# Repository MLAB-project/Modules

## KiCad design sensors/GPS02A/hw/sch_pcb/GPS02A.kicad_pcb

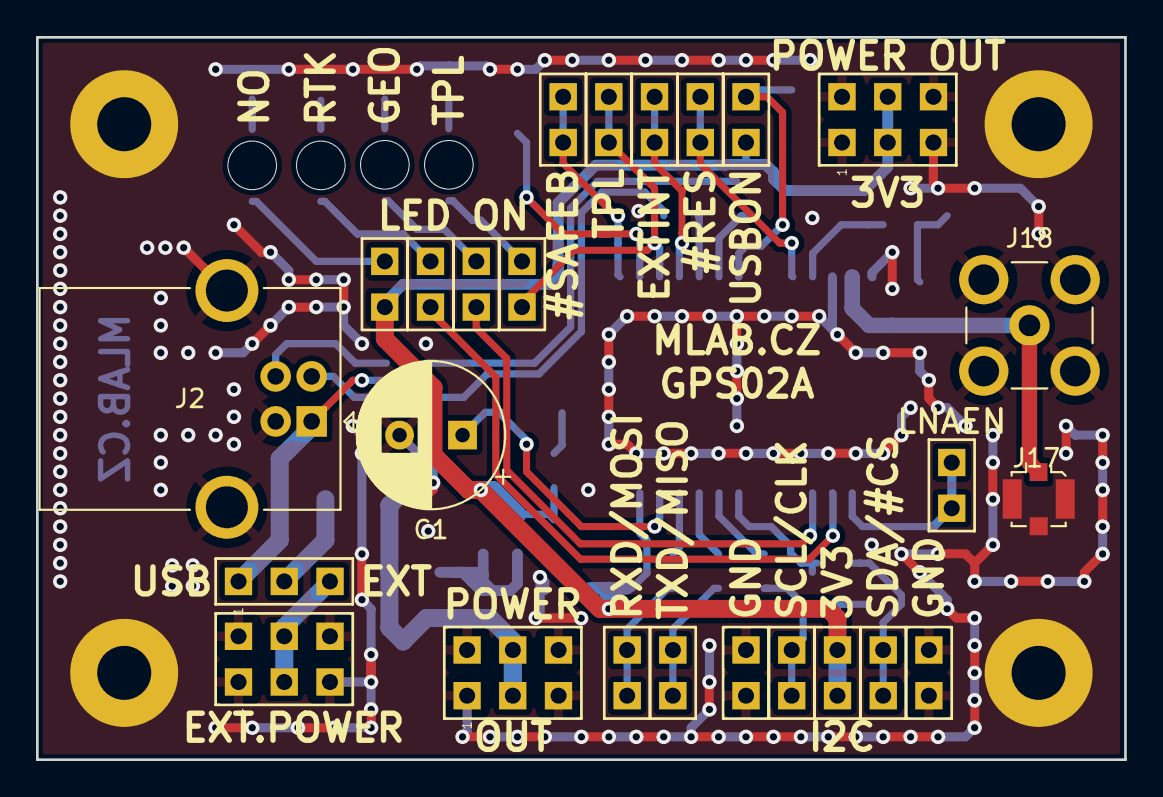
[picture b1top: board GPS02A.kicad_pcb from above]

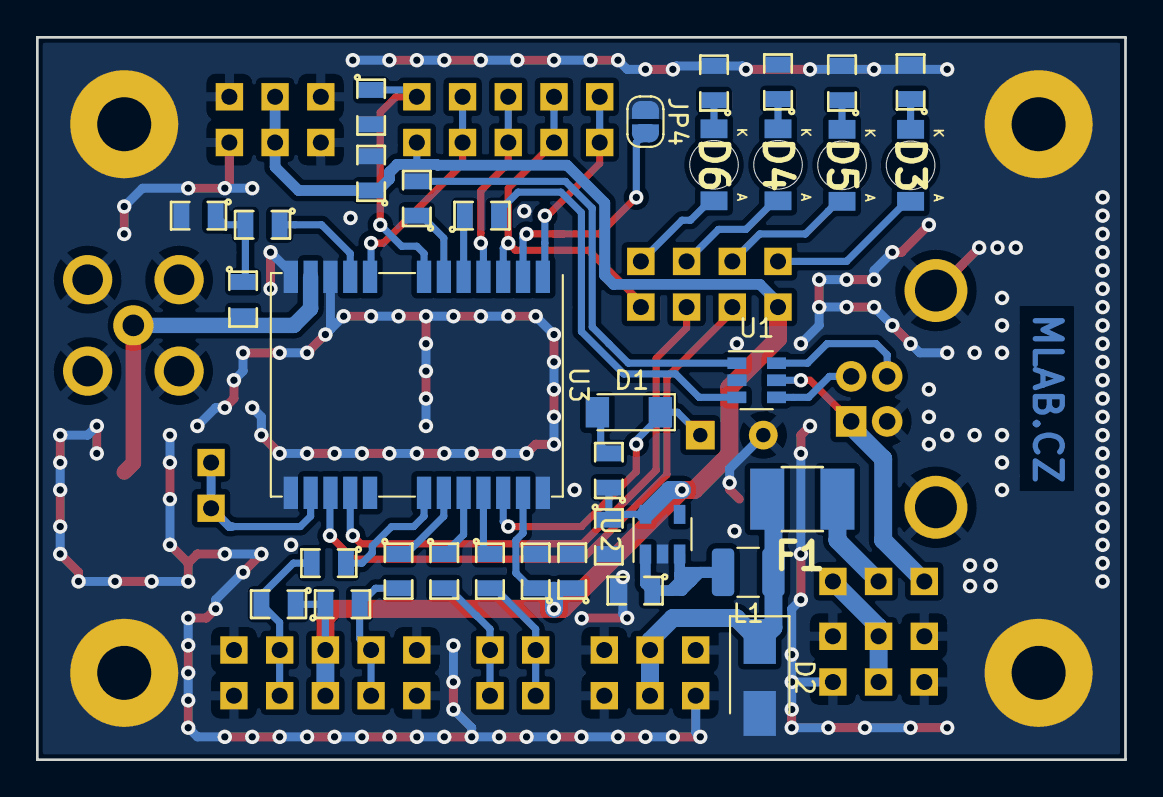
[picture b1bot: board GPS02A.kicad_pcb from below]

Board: 2 copper layers, 60.5 x 40.1 mm, 63 parts (34 on the bottom side), 43 nets.

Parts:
C1: 1F; CP_Radial_D8.0mm_P3.50mm
C2: 10uF; SMD-0805
C3, C5, C6: 1uF; SMD-0805
C4: 100nF; SMD-0805
C7: 10nF; SMD-0805
D1: BAS85; D_MiniMELF
D2: M4; D_SMA
D3: RED; LED_1206
D4, D5: YELLOW; LED_1206
D6: GREEN; LED_1206
F1: 750mA; 1812
J1, J3, J15: HEADER_2x03_PARALLEL; Straight_2x03
J2: USB_B; USB_B_OST_USB-B1HSxx_Horizontal
J4, J5, J6, J7, J8, J9, J10, J11, J12, J13, J14, J16: HEADER_2x01_PARALLEL; Straight_2x01
J17: u.FL; U.FL_Molex_MCRF_73412-0110_Vertical
J18: SMA; SMB_Jack_Vertical
JP1: Jumper_3_Bridged12; Straight_1x03
JP2, JP6: Jumper_2_Bridged; Straight_1x02
JP4: Jumper_2_Open; SolderJumper-2_P1.3mm_Open_RoundedPad1.0x1.5mm
JP7, JP8, JP9: Jumper_2_Open; Straight_1x02
L1: NL322522T-101K; L_1210_3225Metric
L2: 27nH; SMD-0805
M1, M2, M3, M4: HOLE; MountingHole_3mm
R1: 22R; SMD-0805
R2, R3, R15: 10k; SMD-0805
R4, R5, R6, R7, R8, R9: 33R; SMD-0805
R10, R12, R13, R14: 620R; SMD-0805
R11: 10R; SMD-0805
U1: USBLC6-2SC6; SOT-23-6
U2: MIC5504-3.3YM5; SOT-23-5
U3: NEO-M8P; ublox_NEO

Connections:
+3V3: C3.1, C4.1, C5.1, C6.1, J8.1, J8.2, J15.3, J15.4, JP2.2, JP9.1, R1.1, R2.1, R3.1, U2.5, U3.23
/#RESET: J13.1, J13.2, U3.8
/#SAFEB: J12.1, J12.2, U3.1
/D+: J2.3, U1.6
/D-: J2.2, U1.4
/DM: R4.2, U1.3
/DP: R5.2, U1.1
/D_SEL: JP4.2, U3.2
/EXTINT: J11.1, J11.2, U3.4
/GEO_STAT: D4.2, JP8.2
/LNEN: J14.1, J14.2, U3.14
/RTK_STAT: D5.2, JP7.2
/RXD/MOSI: J5.1, J5.2, R7.2
/SCL/CLK: J7.1, J7.2, R3.2, R9.2
/SDA/#CS: J6.1, J6.2, R2.2, R8.2
/TIMEPULSE: D6.2, JP6.2
/TXD/MISO: J4.1, J4.2, R6.2
/VBACKUP: C1.1, D1.1, U3.22
/VBUS: J2.1, JP1.1, U1.5
/VDD_USB: JP2.1, R15.1, U3.7
GND: C1.2, C2.2, C3.2, C4.2, C5.2, C6.2, C7.2, D2.2, J1.1, J1.2, J1.5, J1.6, J2.4, J2.5, J3.1, J3.2, J3.5, J3.6, J9.1, J9.2, J10.1, J10.2, J15.1, J15.2, J15.5, J15.6, J17.2, J18.2, JP4.1, M1.1, M2.1, M3.1, M4.1, R10.2, R12.2, R13.2, R14.2, R15.2, U1.2, U2.2, U3.10, U3.12, U3.13, U3.24
unnamed: C2.1, L1.2, U2.1, U2.3
unnamed: C7.1, L2.1, R11.2
unnamed: D1.2, R1.2
unnamed: D2.1, F1.2, J3.3, J3.4, L1.1
unnamed: D3.1, R10.1
unnamed: D3.2, JP9.2
unnamed: D4.1, R12.1
unnamed: D5.1, R13.1
unnamed: D6.1, R14.1
unnamed: F1.1, JP1.2
unnamed: J1.3, J1.4, JP1.3
unnamed: J16.1, J16.2, JP6.1, U3.3
unnamed: J17.1, J18.1, L2.2, U3.11
unnamed: JP7.1, U3.15
unnamed: JP8.1, U3.16
unnamed: R4.1, U3.5
unnamed: R5.1, U3.6
unnamed: R6.1, U3.20
unnamed: R7.1, U3.21
unnamed: R8.1, U3.18
unnamed: R9.1, U3.19
unnamed: R11.1, U3.9

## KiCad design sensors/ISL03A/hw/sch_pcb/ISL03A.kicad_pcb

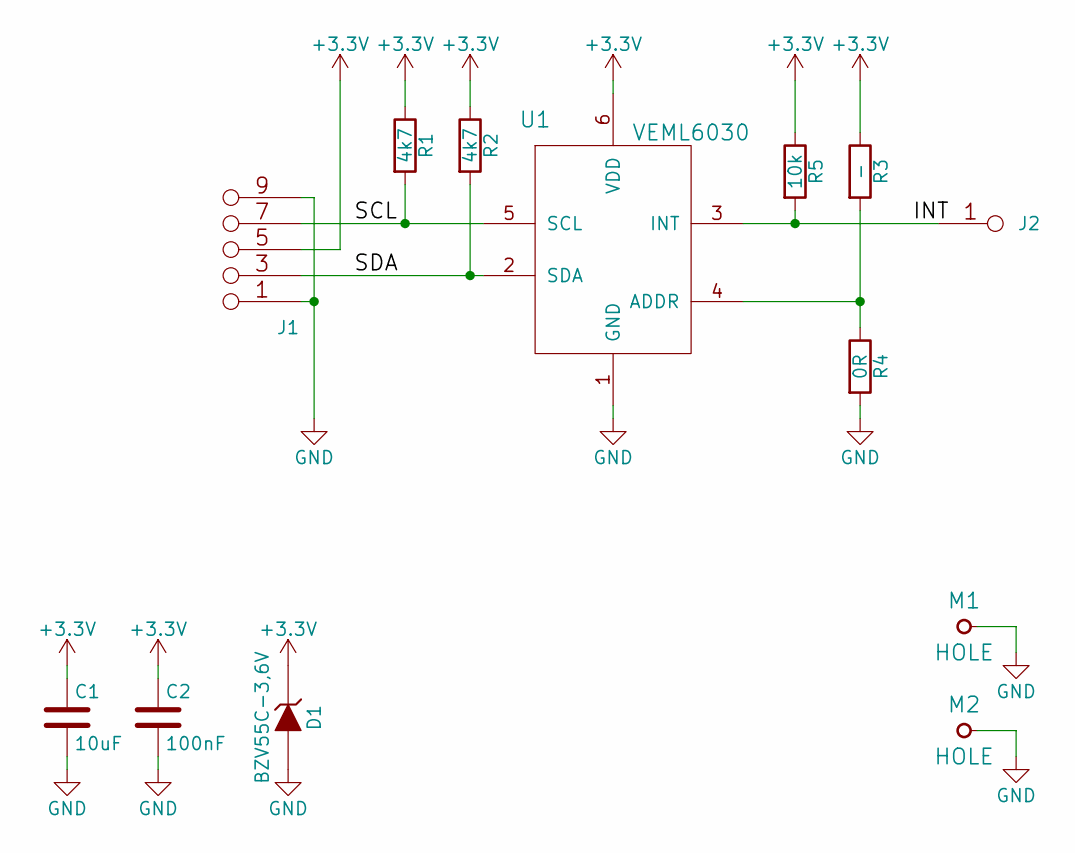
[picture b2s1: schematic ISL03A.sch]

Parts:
C1: 10uF; SMD-0805
C2: 100nF; SMD-0805
D1: BZV55C-3,6V; Diode-MiniMELF_Standard
J1: JUMP_5X2; Straight_2x05
J2: CONN1_1; Straight_1x01
M1, M2: HOLE; MountingHole_3mm
R1, R2: 4k7; SMD-0805
R3: -; SMD-0805
R4: 0R; SMD-0805
R5: 10k; SMD-0805
U1: VEML6030

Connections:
+3V3: C1.1, C2.1, D1.2 (K), J1.5 (6), J1.6, R1.1, R2.1, R3.1, R5.1, U1.6 (VDD)
/INT: J2.1, R5.2, U1.3 (INT)
/SCL: J1.7, J1.8 (7), R1.2, U1.5 (SCL)
/SDA: J1.3 (4), J1.4, R2.2, U1.2 (SDA)
GND: C1.2, C2.2, D1.1 (A), J1.1 (2), J1.2, J1.9 (10), J1.10, M1.1, M2.1, R4.2, U1.1 (GND)
unnamed: R3.2, R4.1, U1.4 (ADDR)

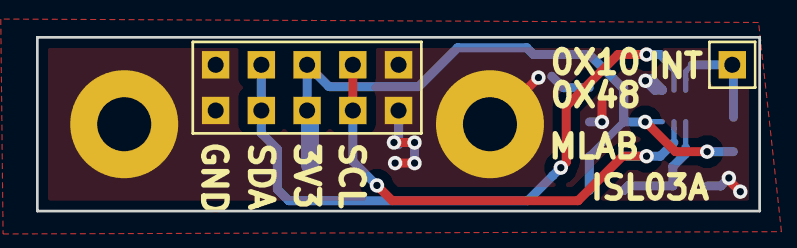
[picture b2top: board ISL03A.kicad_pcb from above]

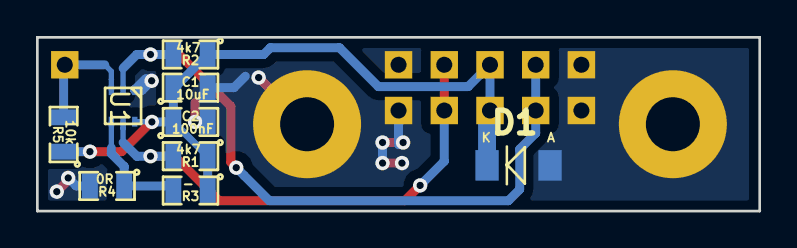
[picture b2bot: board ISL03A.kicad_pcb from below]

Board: 2 copper layers, 40.1 x 9.7 mm, 13 parts (9 on the bottom side), 6 nets.

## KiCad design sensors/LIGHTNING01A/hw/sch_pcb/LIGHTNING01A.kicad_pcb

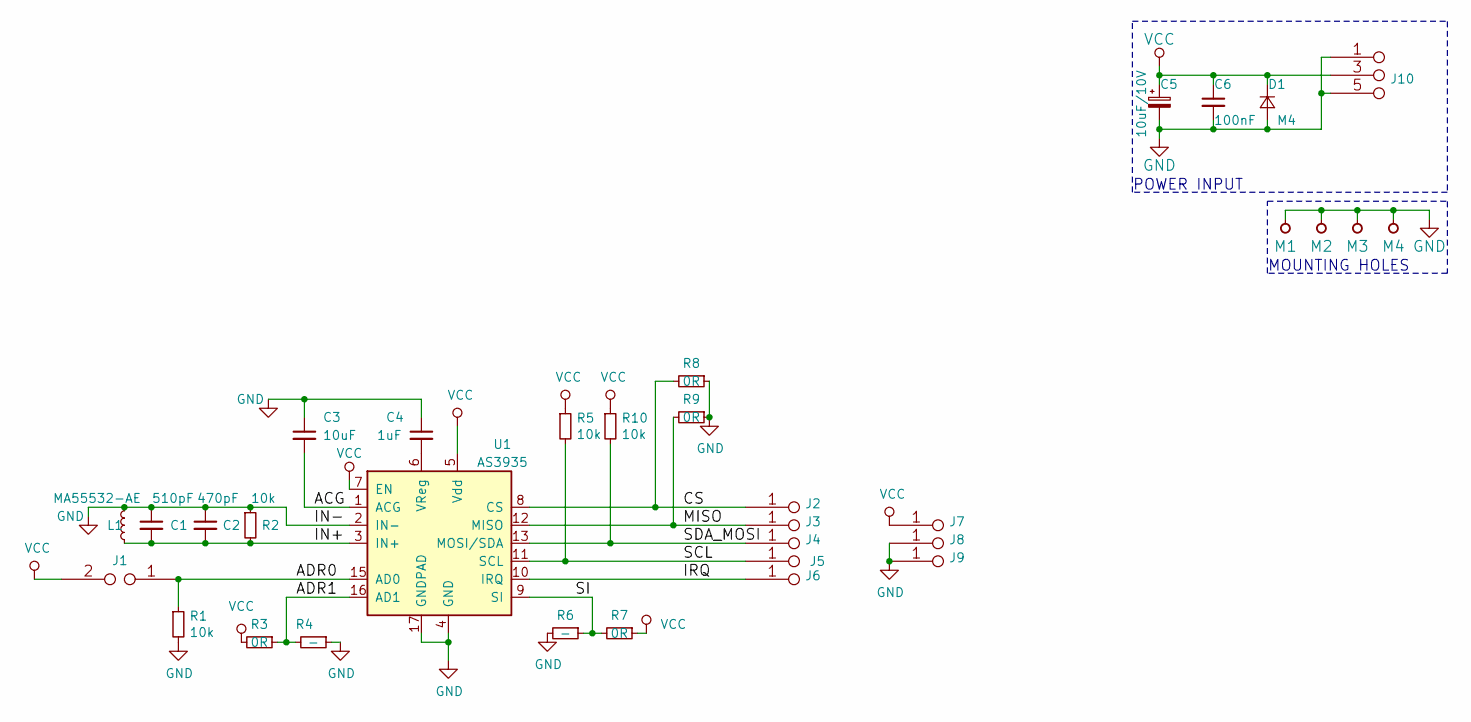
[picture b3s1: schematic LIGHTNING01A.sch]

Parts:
C1: 510pF; SMD-0805
C2: 470pF; SMD-0805
C3: 10uF; SMD-0805
C4: 1uF; SMD-0805
C5: 10uF/10V; SMD-0805
C6: 100nF; SMD-0805
D1: M4; Diode-MELF_Standard
J1: JUMP2_2x1; Straight_2x01
J2, J3, J4, J5, J6, J7, J8, J9: JUMP_2x1; Straight_2x01
J10: JUMP_3X2; Straight_2x03
L1: MA55532-AE; Coilcraft_MA5532-AE_RFID
M1, M2, M3, M4: HOLE; MountingHole_3mm
R1, R2, R5, R10: 10k; SMD-0805
R3, R7, R8, R9: 0R; SMD-0805
R4, R6: -; SMD-0805
U1: AS3935; MLPQ-16

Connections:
/ACG: C3.2, U1.1 (ACG)
/ADR0: J1.1, R1.1, U1.15 (AD0)
/ADR1: R3.1, R4.2, U1.16 (AD1)
/CS: J2.1, J2.2, R8.2, U1.8 (CS)
/IN+: C1.2, C2.2, L1.1, R2.2, U1.3 (IN+)
/IRQ: J6.1, J6.2, U1.10 (IRQ)
/MISO: J3.1, J3.2, R9.2, U1.12 (MISO)
/SCL: J5.1, J5.2, R5.2, U1.11 (SCL)
/SDA_MOSI: J4.1, J4.2, R10.2, U1.13 (MOSI/SDA)
/SI: R6.1, R7.2, U1.9 (SI)
GND: C1.1, C2.1, C3.1, C4.1, C5.2, C6.2, D1.2 (A), J8.1, J8.2, J9.1, J9.2, J10.1 (2), J10.2, J10.5 (6), J10.6, L1.2, M1.1, M2.1, M3.1, M4.1, R1.2, R2.1, R4.1, R6.2, R8.1, R9.1, U1.2 (IN-), U1.4 (GND), U1.17 (GNDPAD)
unnamed: C4.2, U1.6 (VReg)
VCC: C5.1, C6.1, D1.1 (K), J1.2, J7.1, J7.2, J10.3 (4), J10.4, R3.2, R5.1, R7.1, R10.1, U1.5 (Vdd), U1.7 (EN)

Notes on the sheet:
POWER INPUT
MOUNTING HOLES

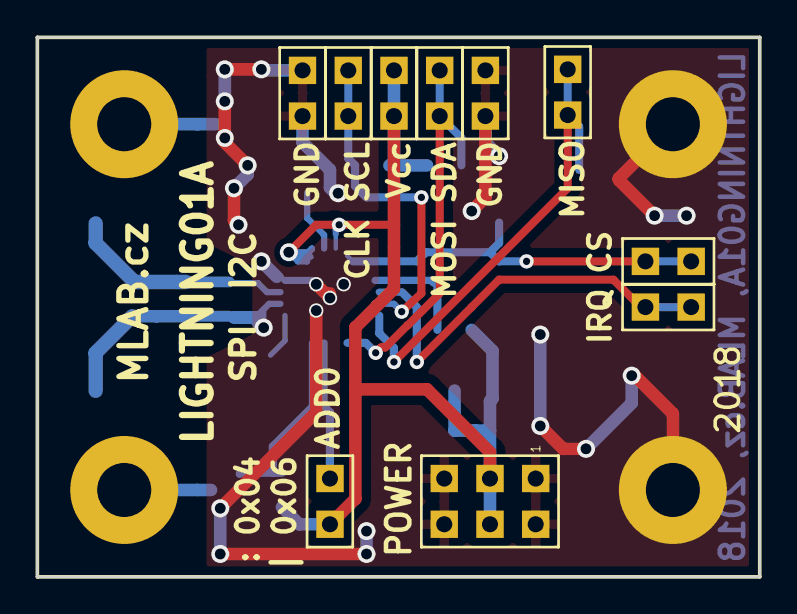
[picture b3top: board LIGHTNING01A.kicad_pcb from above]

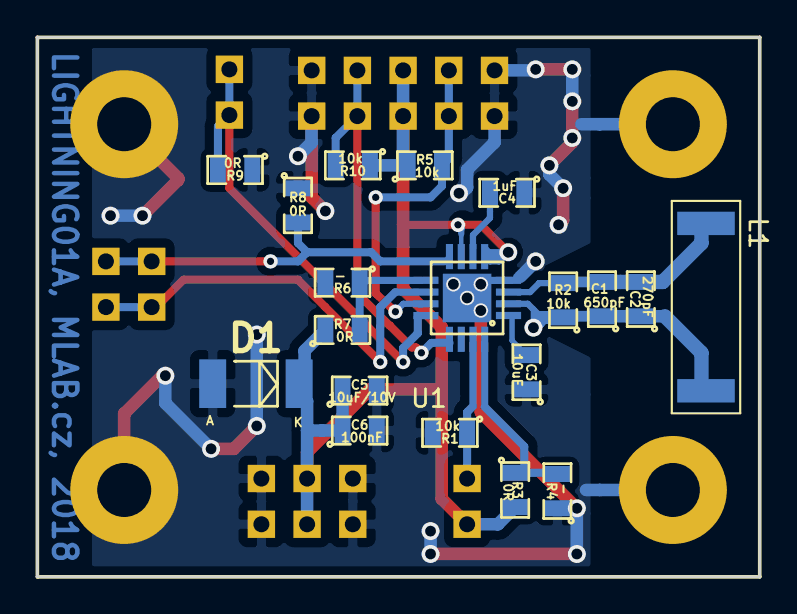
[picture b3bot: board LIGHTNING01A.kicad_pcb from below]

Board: 2 copper layers, 40.1 x 30.0 mm, 33 parts (19 on the bottom side), 13 nets.

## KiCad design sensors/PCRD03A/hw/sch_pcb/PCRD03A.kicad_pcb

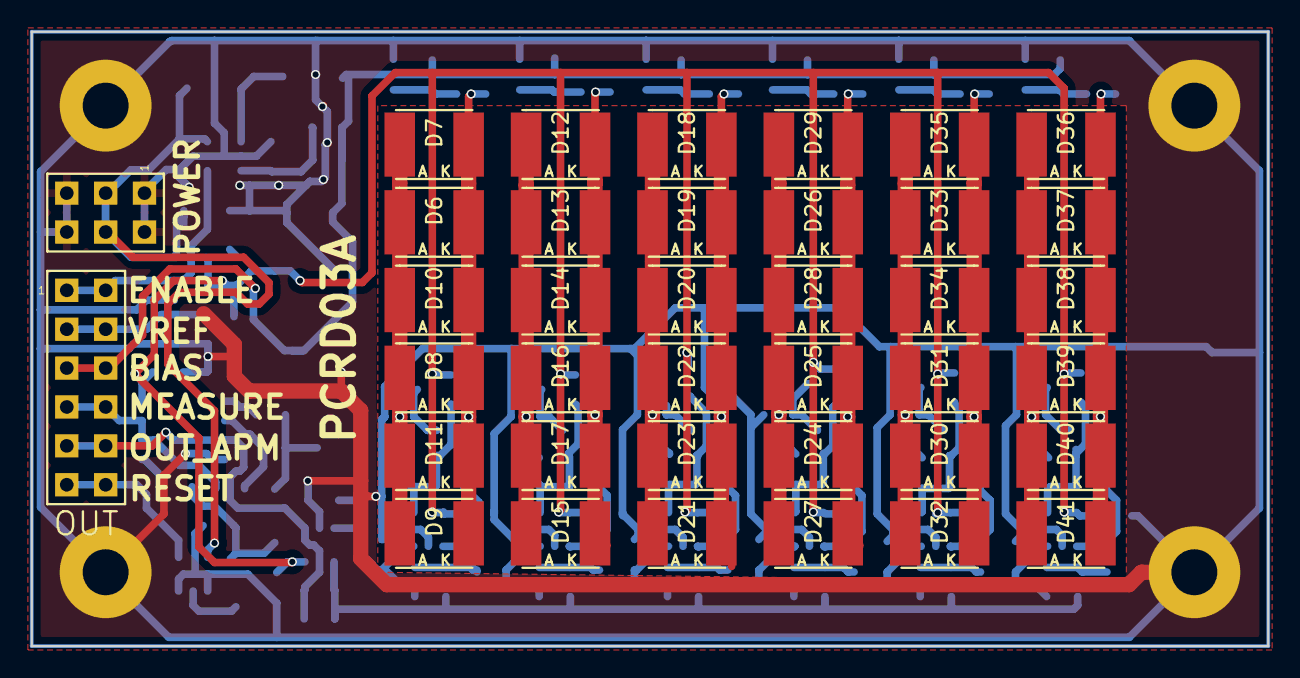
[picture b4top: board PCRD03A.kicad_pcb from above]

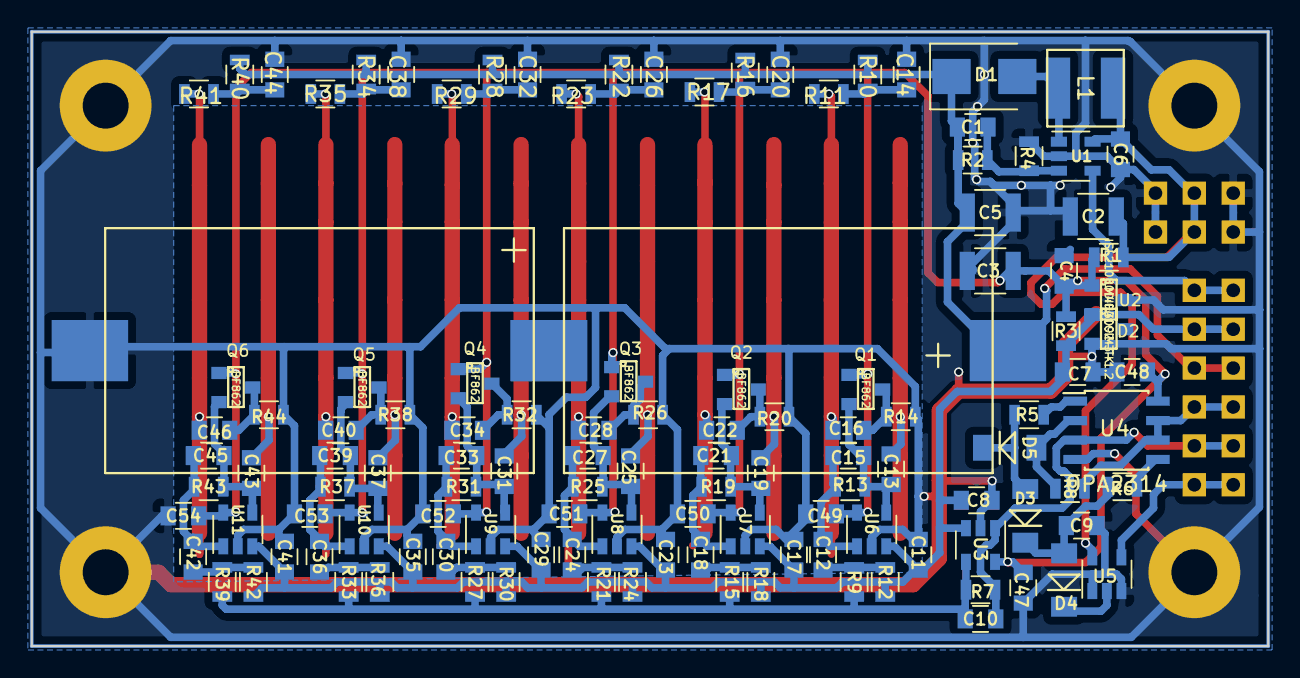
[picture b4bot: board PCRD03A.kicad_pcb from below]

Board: 2 copper layers, 80.8 x 40.1 mm, 165 parts (123 on the bottom side), 61 nets.

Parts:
BT1, BT2: Battery_Cell; CH28-2032
C1: 22p; C_0805
C2, C3, C5: 47u/16V; C_1210
C4, C7, C47, C48, C49, C50, C51, C52, C53, C54: 100n; C_0805
C6, C8, C11, C16, C17, C22, C23, C28, C29, C34, C35, C40, C41, C46: 4u7; C_0805
C9, C13, C19, C25, C31, C37, C43: 1n; C_0805
C10: 2n2; C_0805
C12, C14, C18, C20, C24, C26, C30, C32, C36, C38, C42, C44: 1u; C_0805
C15, C21, C27, C33, C39, C45: 1p; C_0805
D1: STPS1L30U; D_SMB
D2: LM4041CIM3-1.2; SOT-23
D3, D4, D5: 1N4148; Diode-MiniMELF_Standard
D6, D7, D8, D9, D10, D11, D12, D13, D14, D15, D16, D17, D18, D19, D20, D21, D22, D23, D24, D25, D26, D27, D28, D29, D30, D31, D32, D33, D34, D35, D36, D37, D38, D39, D40, D41: D_Photo; PIND_universal
J1: POWER; Straight_2x03
J2: OUT; Straight_2x06
L1: 10u; DJNR5040
M1, M2, M3, M4: HOLE; MountingHole_3mm
Q1, Q2, Q3, Q4, Q5, Q6: BF862; SOT-23
R1: 100/10; R_0805
R2: 470k; R_0805
R3, R10, R11, R16, R17, R22, R23, R28, R29, R34, R35, R40, R41: 4k7; R_0805
R4: 120k; R_0805
R5, R6, R8, R9, R15, R21, R27, R33, R39: 1k; R_0805
R7: 22k; R_0805
R12, R14, R18, R20, R24, R26, R30, R32, R36, R38, R42, R44: 3k3; R_0805
R13, R19, R25, R31, R37, R43: 10M; R_0805
U1: TPS6104; SOT-23-5
U2: ISL21080DIH309Z-TK; SOT-23
U3, U6, U7, U8, U9, U10, U11: OPA314; SOT-23-5
U4: OPA2314; SOIC-8_3.9x4.9mm_Pitch1.27mm
U5: TS5A4594; SOT-23-5

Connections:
+3V3: C3.1, C4.1, C47.1, C48.1, C49.1, C50.1, C51.1, C52.1, C53.1, C54.1, Q1.1, Q2.1, Q3.1, Q4.1, Q5.1, Q6.1, R1.1, R3.2, U2.1, U3.5, U4.8, U6.5, U7.5, U8.5, U9.5, U10.5, U11.5
+BATT: C2.1, C6.1, J1.3, J1.4, L1.1, R1.2, U1.5, U5.5
/BIAS: BT1.1, C1.1, C5.1, D1.1, J2.5, J2.6, R2.1, R10.2, R16.2, R22.2, R28.2, R34.2, R40.2
/ENABLE: J2.1, J2.2, U1.4
/MEASURE: J2.7, J2.8, R8.1, U4.6, U4.7
/OUT_AMP: C10.1, J2.9, J2.10, R7.1, U3.1, U4.3
/RESET: J2.11, J2.12, U5.4
/VREF: C7.1, C8.2, C11.2, C17.2, C23.2, C29.2, C35.2, C41.2, D2.1, J2.3, J2.4, R3.1, R12.1, R18.1, R24.1, R30.1, R36.1, R42.1, U2.2, U3.3, U6.3, U7.3, U8.3, U9.3, U10.3, U11.3
/charge_amp1/OUT: C10.2, R7.2, R9.1, R15.1, R21.1, R27.1, R33.1, R39.1, U3.4
GND: BT2.2, C2.2, C3.2, C4.2, C5.2, C6.2, C7.2, C8.1, C9.2, C11.1, C14.1, C17.1, C20.1, C23.1, C26.1, C29.1, C32.1, C35.1, C38.1, C41.1, C44.1, C47.2, C48.2, C49.2, C50.2, C51.2, C52.2, C53.2, C54.2, D2.2, J1.1, J1.2, J1.5, J1.6, M1.1, M2.1, M3.1, M4.1, R4.2, R14.1, R20.1, R26.1, R32.1, R38.1, R44.1, U1.2, U2.3, U3.2, U4.4, U5.1, U5.3, U6.2, U7.2, U8.2, U9.2, U10.2, U11.2
unnamed: BT1.2, BT2.1
unnamed: C1.2, R2.2, R4.1, U1.3
unnamed: C9.1, D3.1, D4.2, R6.2
unnamed: C12.1, C15.1, R13.1, U6.1
unnamed: C12.2, R9.2, R12.2
unnamed: C13.1, D6.2, D7.2, D8.2, D9.2, D10.2, D11.2
unnamed: C13.2, C15.2, Q1.2, R13.2, U6.4
unnamed: C14.2, R10.1, R11.2
unnamed: C16.1, D6.1, D7.1, D8.1, D9.1, D10.1, D11.1, R11.1
unnamed: C16.2, Q1.3, R14.2
unnamed: C18.1, C21.1, R19.1, U7.1
unnamed: C18.2, R15.2, R18.2
unnamed: C19.1, D12.2, D13.2, D14.2, D15.2, D16.2, D17.2
unnamed: C19.2, C21.2, Q2.2, R19.2, U7.4
unnamed: C20.2, R16.1, R17.2
unnamed: C22.1, D12.1, D13.1, D14.1, D15.1, D16.1, D17.1, R17.1
unnamed: C22.2, Q2.3, R20.2
unnamed: C24.1, C27.1, R25.1, U8.1
unnamed: C24.2, R21.2, R24.2
unnamed: C25.1, D18.2, D19.2, D20.2, D21.2, D22.2, D23.2
unnamed: C25.2, C27.2, Q3.2, R25.2, U8.4
unnamed: C26.2, R22.1, R23.2
unnamed: C28.1, D18.1, D19.1, D20.1, D21.1, D22.1, D23.1, R23.1
unnamed: C28.2, Q3.3, R26.2
unnamed: C30.1, C33.1, R31.1, U9.1
unnamed: C30.2, R27.2, R30.2
unnamed: C31.1, D24.2, D25.2, D26.2, D27.2, D28.2, D29.2
unnamed: C31.2, C33.2, Q4.2, R31.2, U9.4
unnamed: C32.2, R28.1, R29.2
unnamed: C34.1, D24.1, D25.1, D26.1, D27.1, D28.1, D29.1, R29.1
unnamed: C34.2, Q4.3, R32.2
unnamed: C36.1, C39.1, R37.1, U10.1
unnamed: C36.2, R33.2, R36.2
unnamed: C37.1, D30.2, D31.2, D32.2, D33.2, D34.2, D35.2
unnamed: C37.2, C39.2, Q5.2, R37.2, U10.4
unnamed: C38.2, R34.1, R35.2
unnamed: C40.1, D30.1, D31.1, D32.1, D33.1, D34.1, D35.1, R35.1
unnamed: C40.2, Q5.3, R38.2
unnamed: C42.1, C45.1, R43.1, U11.1
unnamed: C42.2, R39.2, R42.2
unnamed: C43.1, D36.2, D37.2, D38.2, D39.2, D40.2, D41.2
unnamed: C43.2, C45.2, Q6.2, R43.2, U11.4
unnamed: C44.2, R40.1, R41.2
unnamed: C46.1, D36.1, D37.1, D38.1, D39.1, D40.1, D41.1, R41.1
unnamed: C46.2, Q6.3, R44.2
unnamed: D1.2, L1.2, U1.1
unnamed: D3.2, D5.1, R5.1
unnamed: D4.1, U5.2
unnamed: D5.2, R8.2, U4.2
unnamed: R5.2, U4.1
unnamed: R6.1, U4.5

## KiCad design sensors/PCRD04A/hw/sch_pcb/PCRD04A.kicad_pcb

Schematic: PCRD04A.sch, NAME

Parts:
BT1: CH28-2032
C1: 47uF; TantalC_SizeC_Reflow
C2: 1uF/36V; SMD-0805
C3, C17: 4u7; SMD-0805
C4, C6, C7, C8, C9: 10uF; SMD-0805
C5: 1pF - 251R15S1R0AV4E; SMD-0805
C10, C11, C12, C13, C14, C16, C20: 100nF; SMD-0805
C15: 3n3; SMD-0805
C18: 2n2; SMD-0805
C19: 1nF; SMD-0805
D1: M4; Diode-SMA_Standard
D2: D_Photo; HAMAMATSU_S2744-09
J1: 3.6V; Straight_2x03
J2, J3, J4, J5, J6, J7: HEADER_2x01_PARALLEL; Straight_2x01
J8: HEADER_2x03_PARALLEL; Straight_2x03
J9: HEADER_1x02; Straight_1x02
J10: HEADER_1x02; Straight_2x02
M1, M2, M3, M4, M5, M6: HOLE; MountingHole_3mm
R1, R11, R14: 4k7; SMD-0805
R2, R3, R4, R5: 100; SMD-0805
R6: 10M; SMD-0805
R7, R12: 10k; SMD-0805
R8, R10: 1k; SMD-0805
R9: 15k; SMD-0805
R13: 2k2; SMD-0805
R15: -; SMD-0805
U1, U2: OPA2314; SOIC-8_3.9x4.9mm_Pitch1.27mm
U3: ISL21080DIH312Z-TK 1V25; SOT-23
U4: TS7211; SOT-23-5_HandSoldering
U5: TS5A4594; SOT-23-5_HandSoldering
U6: LM4041CIM3-1.2(neosazovat); SOT-23

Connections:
/#PeakDetect/Trace: J3.1, J3.2, R12.1, U5.4
/A: C5.2, D2.2, J10.2, R6.2, U1.2
/A/D: J6.1, J6.2, U2.6, U2.7, U4.4
/BAT+: BT1.1, D2.1, J9.2, J10.1, R14.2
/BAT-: BT1.2, C3.1, C17.1, C20.1, J9.1, R7.1, R8.2, R15.1, U1.3, U2.3, U3.2 (Vout), U6.1
/Ubias: J8.3, J8.4, R1.1
/VCC1: C6.1, C11.1, R2.1, U1.8
/VCC2: C7.1, C12.1, R3.1, U2.8
/VCC3: C8.1, C13.1, R4.1, U4.2
/VCC4: C9.1, C14.1, R5.1, U5.5
GND: C1.2, C2.2, C3.2, C4.2, C6.2, C7.2, C8.2, C9.2, C11.2, C12.2, C13.2, C14.2, C17.2, C19.2, C20.2, D1.2, J1.1, J1.2, J1.5, J1.6, J2.1, J2.2, J4.1, J4.2, J5.1, J5.2, J7.1, J7.2, J8.1, J8.2, J8.5, J8.6, M1.1, M2.1, M3.1, M4.1, M5.1, M6.1, U1.4, U2.4, U3.3 (GND), U4.5, U5.3, U6.2
unnamed: C2.1, R1.2, R14.1
unnamed: C10.1, R7.2, U1.5
unnamed: C5.1, C10.2, R6.1, U1.1
unnamed: C15.1, C16.2, R9.1, U1.7
unnamed: C15.2, R8.1, R9.2, U1.6
unnamed: C16.1, R10.2
unnamed: C18.1, R11.1, U2.1, U4.3, U5.1
unnamed: C18.2, R10.1, R11.2, U2.2
unnamed: C19.1, R13.1, U2.5
unnamed: R12.2, U4.1
unnamed: R13.2, U5.2
VCC: C1.1, C4.1, D1.1, J1.3, J1.4, R2.2, R3.2, R4.2, R5.2, R15.2, U3.1 (Vin)

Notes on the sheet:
POWER INPUT
MOUNTING HOLES
CR2032

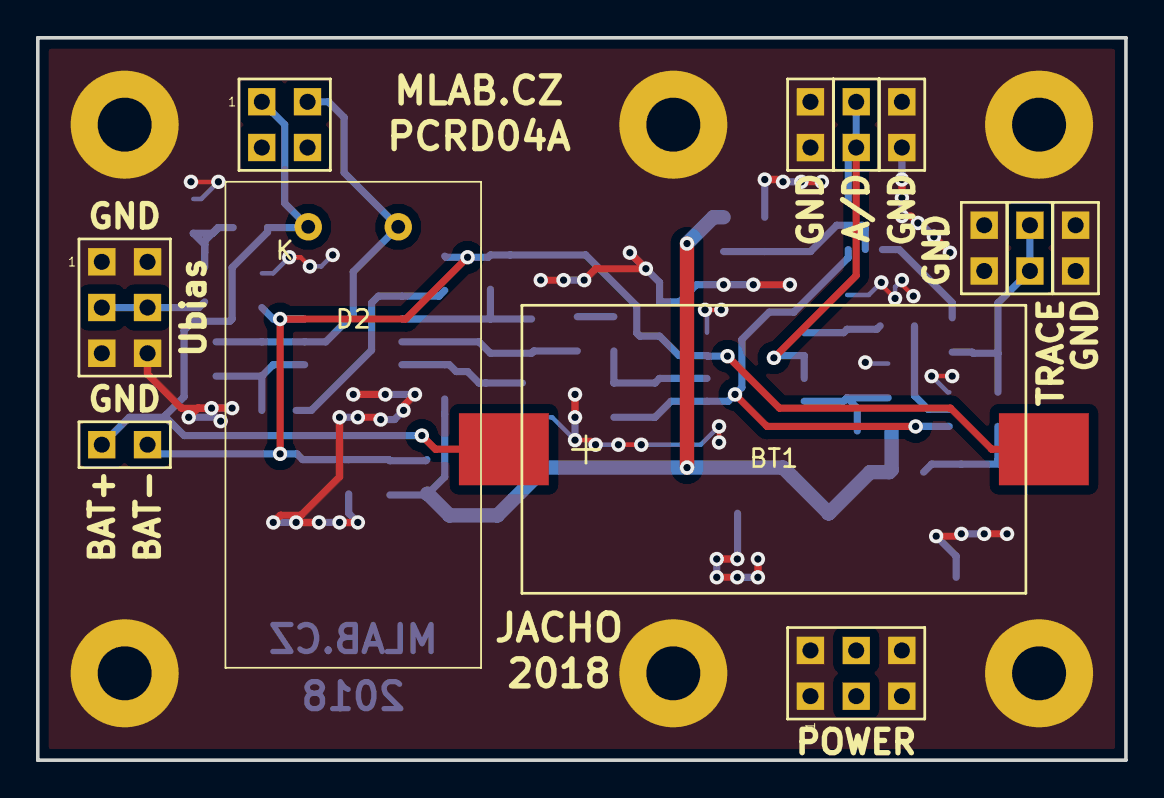
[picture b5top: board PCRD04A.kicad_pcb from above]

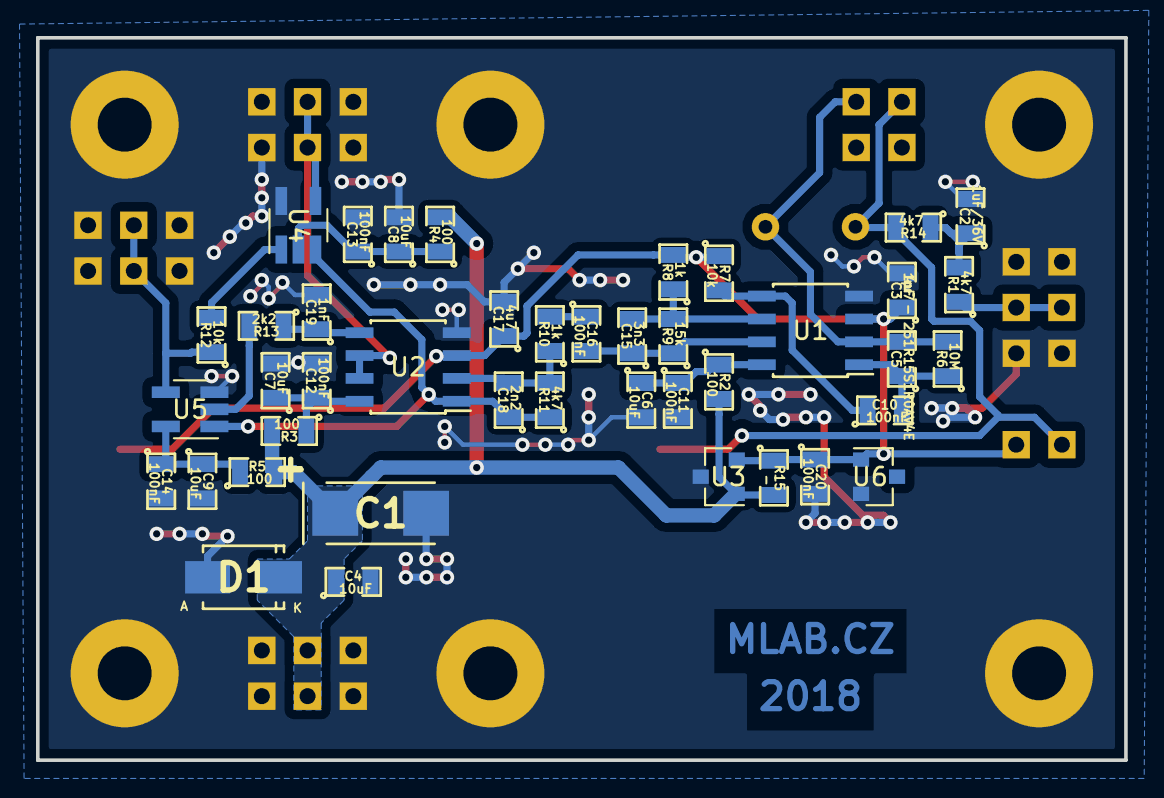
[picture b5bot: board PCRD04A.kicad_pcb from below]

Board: 2 copper layers, 60.5 x 40.1 mm, 60 parts (42 on the bottom side), 23 nets.

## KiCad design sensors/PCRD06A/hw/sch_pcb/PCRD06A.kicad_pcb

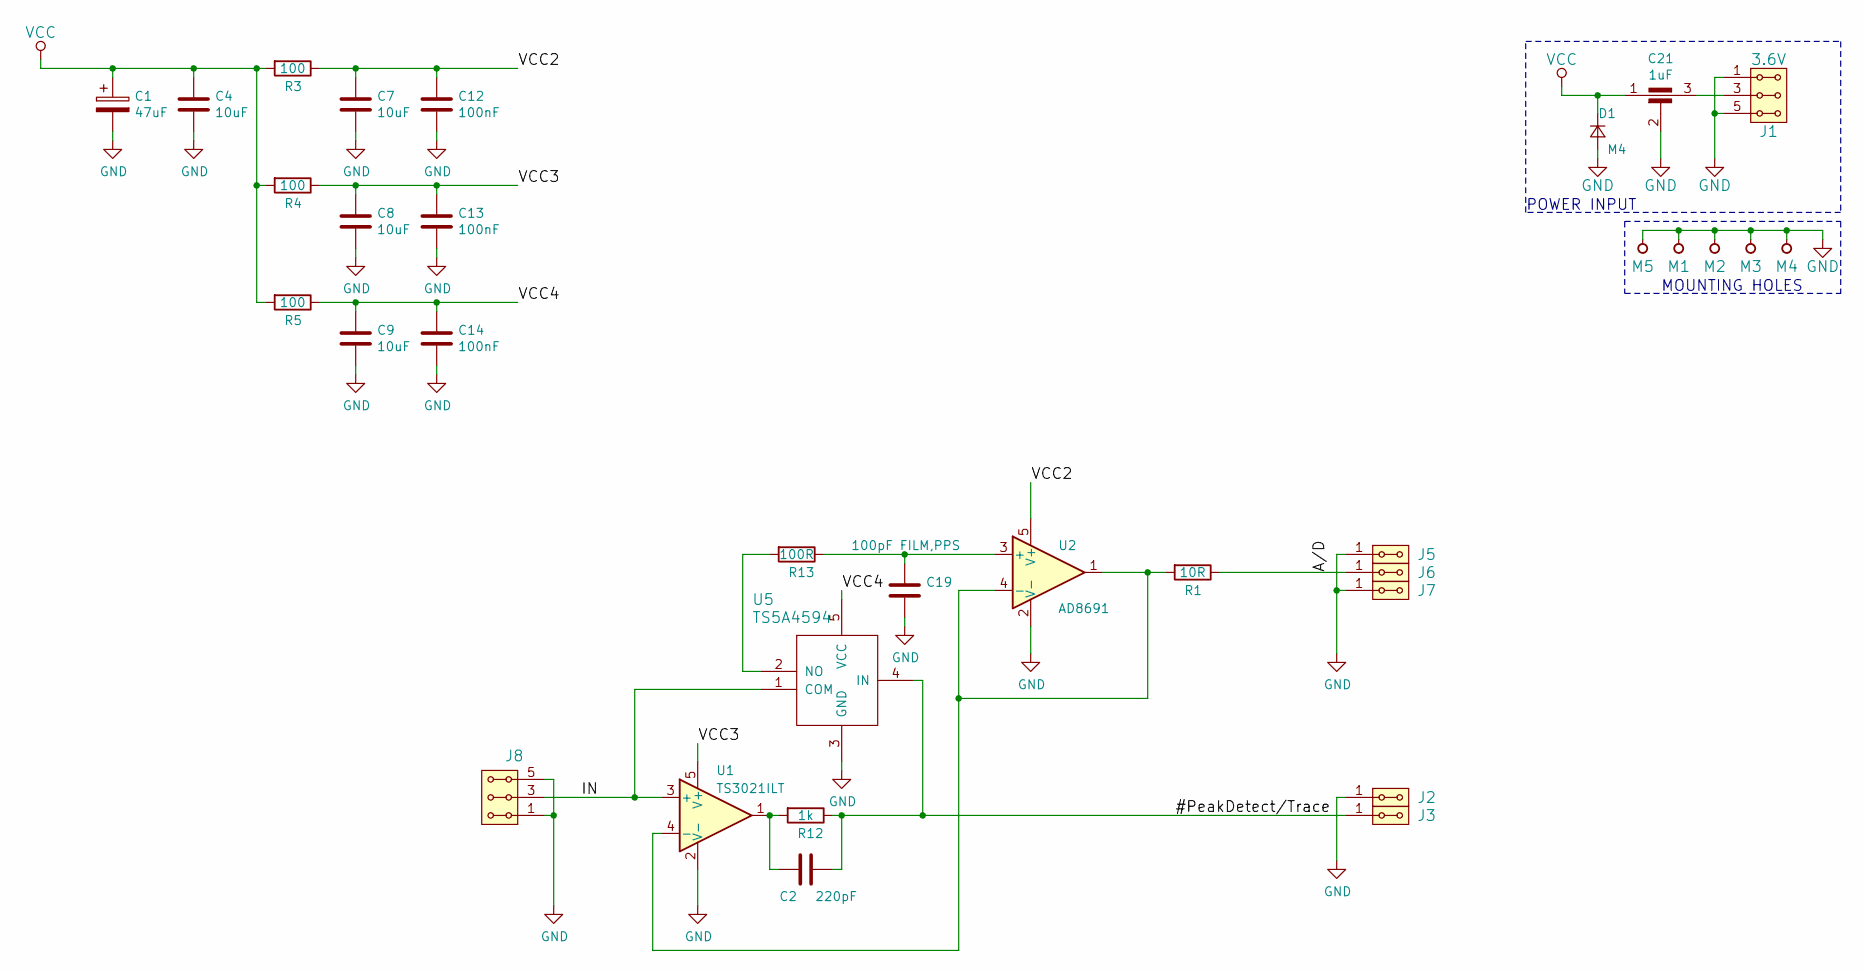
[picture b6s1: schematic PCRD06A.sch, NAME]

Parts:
C1: 47uF; TantalC_SizeC_Reflow
C2: 220pF; SMD-0805
C4, C7, C8, C9: 10uF; SMD-0805
C12, C13, C14: 100nF; SMD-0805
C19: 100pF FILM,PPS; SMD-0805
C21: 1uF; FIR_0805
D1: M4; Diode-SMA_Standard
J1: 3.6V; Straight_2x03
J2, J3, J5, J6, J7: HEADER_2x01_PARALLEL; Straight_2x01
J8: HEADER_2x03_PARALLEL; Straight_2x03
M1, M2, M3, M4: HOLE; MountingHole_3mm
M5: HOLE; Laird_Technologies_BMI-S-204-F_32.00x32.00mm
R1: 10R; SMD-0805
R3, R4, R5: 100; SMD-0805
R12: 1k; SMD-0805
R13: 100R; SMD-0805
U1: TS3021ILT; SOT-23-5_HandSoldering
U2: AD8691; TSOT-23-5_HandSoldering
U5: TS5A4594; SOT-23-5_HandSoldering

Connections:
/#PeakDetect/Trace: C2.1, J3.1, J3.2, R12.1, U5.4 (IN)
/A/D: J6.1, J6.2, R1.1
/IN: J8.3, J8.4, U1.3 (+), U5.1 (COM)
/VCC2: C7.1, C12.1, R3.1, U2.5 (V+)
/VCC3: C8.1, C13.1, R4.1, U1.5 (V+)
/VCC4: C9.1, C14.1, R5.1, U5.5 (VCC)
GND: C1.2, C4.2, C7.2, C8.2, C9.2, C12.2, C13.2, C14.2, C19.2, C21.2, D1.2 (A), J1.1, J1.2, J1.5, J1.6, J2.1, J2.2, J5.1, J5.2, J7.1, J7.2, J8.1, J8.2, J8.5, J8.6, M1.1, M2.1, M3.1, M4.1, M5.1, U1.2 (V-), U2.2 (V-), U5.3 (GND)
unnamed: C2.2, R12.2, U1.1
unnamed: C19.1, R13.1, U2.3 (+)
unnamed: C21.3, J1.3, J1.4
unnamed: R1.2, U1.4 (-), U2.1, U2.4 (-)
unnamed: R13.2, U5.2 (NO)
VCC: C1.1, C4.1, C21.1, D1.1 (K), R3.2, R4.2, R5.2

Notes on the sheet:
POWER INPUT
MOUNTING HOLES

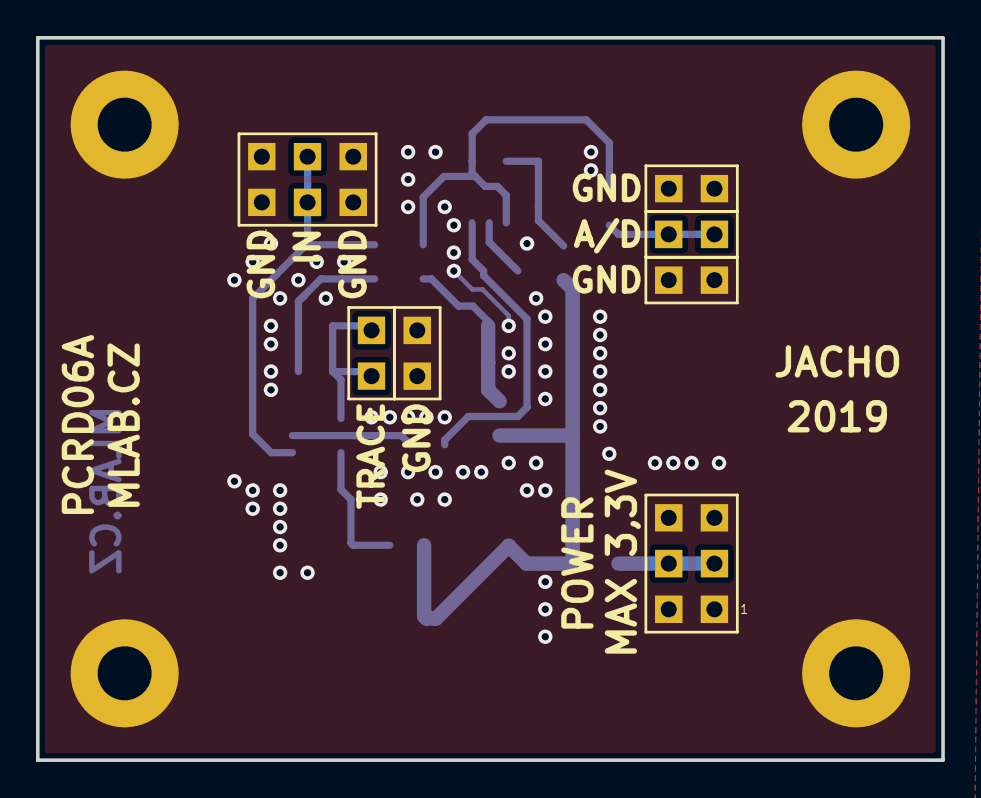
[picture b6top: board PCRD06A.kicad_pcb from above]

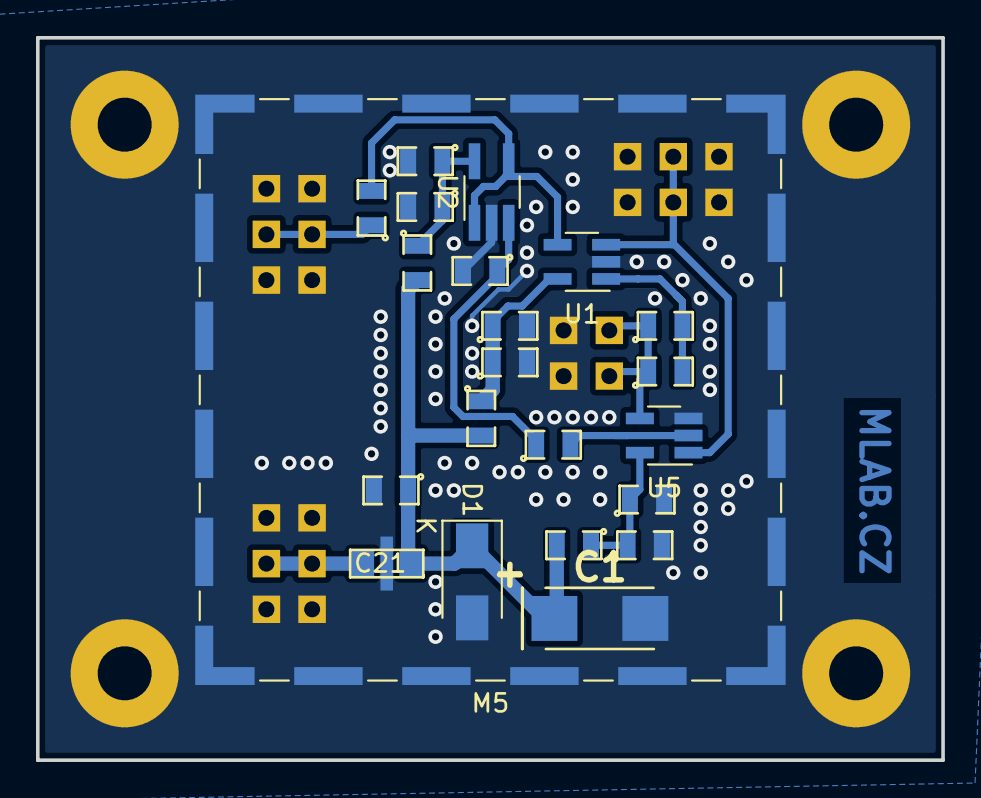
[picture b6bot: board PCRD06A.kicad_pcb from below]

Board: 2 copper layers, 50.3 x 40.1 mm, 33 parts (22 on the bottom side), 13 nets.
